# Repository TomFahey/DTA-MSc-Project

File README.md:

# DTA-MSc-Project

## Description

This repository contains the assorted code and schematics used in the design of a low-cost Differential Thermal Analysis device. This design utilises off-the-shelf parts, in
conjunction with open source software, to provide a kit-based setup allowing users to explore basic application of the DTA technique, in an intuitive and low-cost manner.

## Components

The parts used in this design include:

* Raspberry Pi 4 Model B, running RaspbianOS (buster)
* Raspberrry Pi Pico microcontroller
* Adafruit MAX31865 and MAX31856 temperature sensing breakout boards
* T-type thermocouple
* RTD sensors
* Cytron HAT-MDD10 motor controller board
* Adjustable DC Power Supply
* Custom PCB boards

## Structure

The repository consists of three main parts:

1) The webapp folder contains the python code and .ipynb notebooks which implement the widget-based user interface. This is intended to be run on a small board computer (SBC),
such as a Raspberry Pi Model B (preferably running Raspbian OS), using the JupyterLab web-based interactive development environment. voila-dashboard, is used as a server
extension within Jupyter, for deployment as a standalone web application.
2) The microcontroller folder contains the python code to be run on a CircuitPython compatible microcontroller (Raspberry Pi Pico), which interfaces with the SBC via USB.
3) The pcb folder contains the Autodesk Eagle files for the PCBs used by the system.

The systemd folder contains the configuration files used to automatically launch the service processes which setup the system. These should be placed in ``/etc/systemd/system/``.

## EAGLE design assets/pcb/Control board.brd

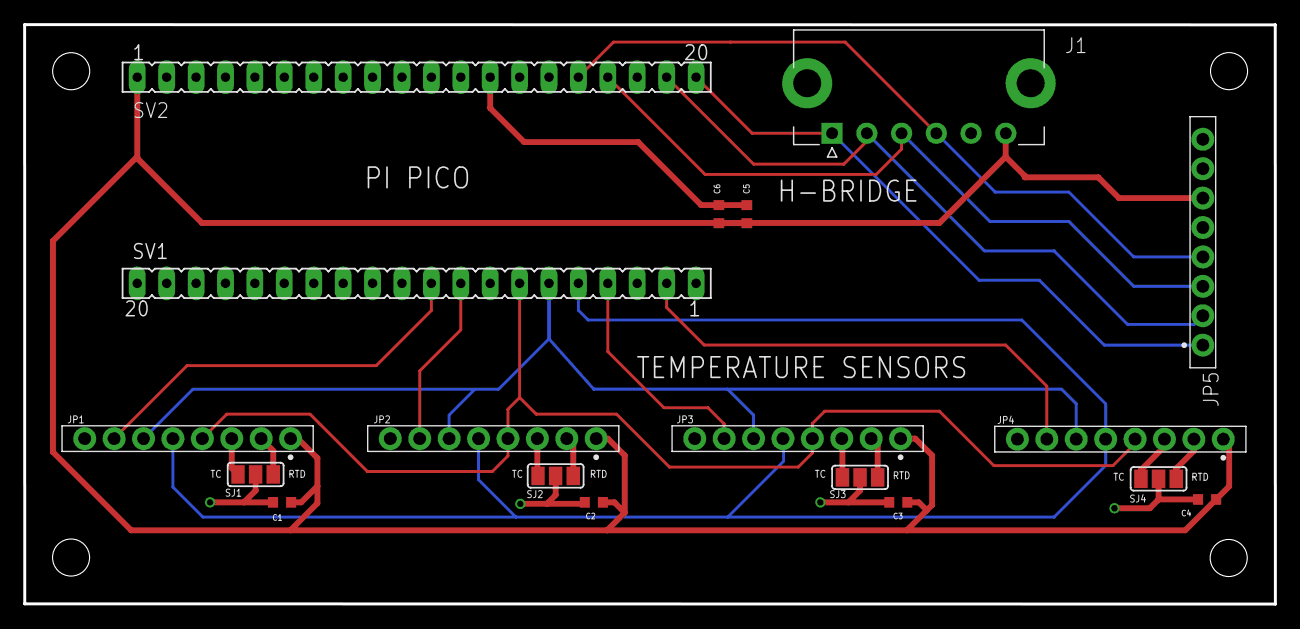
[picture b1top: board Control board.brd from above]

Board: 2 copper layers, 108.0 x 50.0 mm, 18 parts (0 on the bottom side), 21 nets.

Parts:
C1, C2, C3, C4, C5, C6: CL10A105KO8NNNC; CAPC1608X90N
J1: 436500603; MOLEX_436500603
JP1, JP2, JP3, JP4, JP5: HDRVR8W64P254_1X8_2159X200X810B
SJ1, SJ2, SJ3, SJ4: SJ_2
SV1, SV2: FE20

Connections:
+5V: C1.1, C2.1, C3.1, C4.1, C5.1, C6.1, J1.6, JP1.1, JP2.1, JP3.1, JP4.1, JP5.6, SV2.1
CLK: JP1.4, JP2.4, JP3.4, JP4.4, SV1.7
CS0: JP3.7, SV1.4
CS1: JP2.7, SV1.9
CS2: JP1.7, SV1.10
CS3: JP4.7, SV1.2
GND: C1.2, C2.2, C3.2, C4.2, C5.2, C6.2, J1.5, JP5.5, SJ1.2, SJ2.2, SJ3.2, SJ4.2, SV1.3, SV1.8, SV1.13, SV1.18, SV2.3, SV2.8, SV2.13, SV2.18
MISO: JP1.5, JP2.5, JP3.5, JP4.5, SV1.5
MOSI: JP1.6, JP2.6, JP3.6, JP4.6, SV1.6
unnamed: JP4.2, SJ4.1
unnamed: JP1.3, SJ1.3
unnamed: JP1.2, SJ1.1
unnamed: JP2.3, SJ2.3
unnamed: JP2.2, SJ2.1
unnamed: JP3.3, SJ3.3
unnamed: JP3.2, SJ3.1
unnamed: JP4.3, SJ4.3
PWM1: J1.1, JP5.1, SV2.20
PWM2: J1.2, JP5.2, SV2.19
PWM3: J1.3, JP5.3, SV2.17
PWM4: J1.4, JP5.4, SV2.16

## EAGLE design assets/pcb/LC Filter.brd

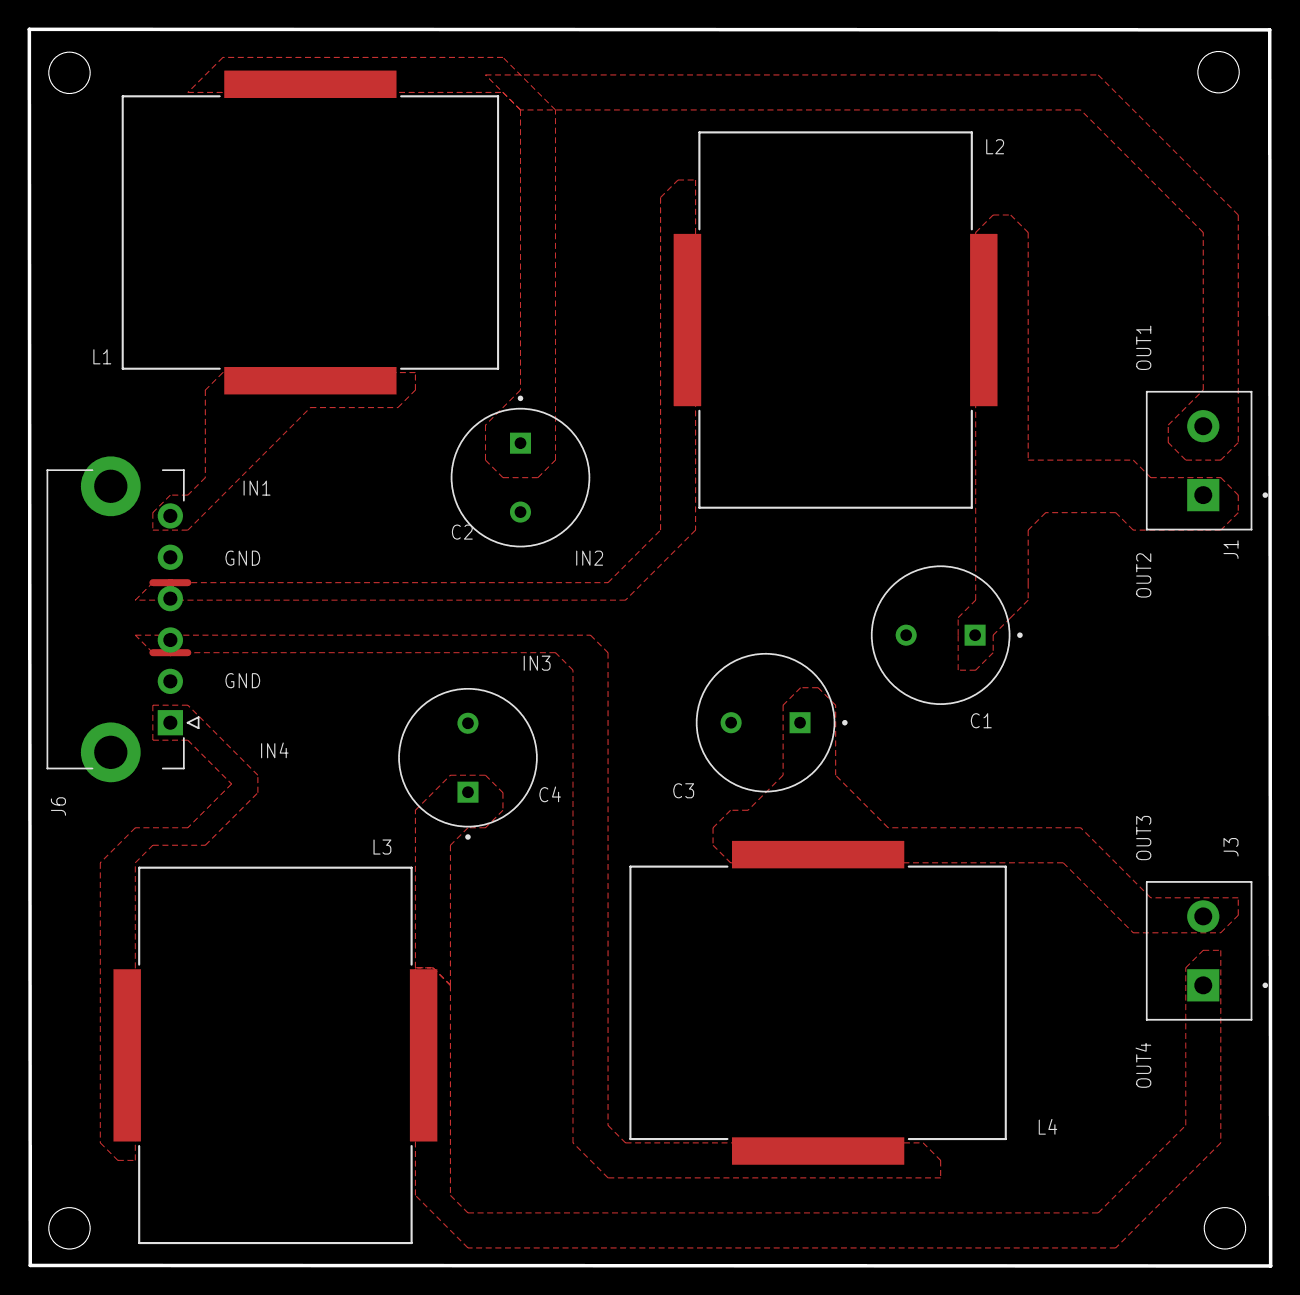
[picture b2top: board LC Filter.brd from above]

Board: 2 copper layers, 90.0 x 89.7 mm, 11 parts (0 on the bottom side), 9 nets.

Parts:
C1, C2, C3, C4: ECA1EHG471E; CAPPRD500W60D1000H1250
J1, J3: TB002-500-02BE; CUI_TB002-500-02BE
J6: 436500603; MOLEX_436500603
L1, L2, L3, L4: 60B104C; 6000B_SERIES_MUR

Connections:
GND: C1.N, C2.N, C3.N, C4.N, J6.2, J6.5
IN1: J6.6, L1.1
IN2: J6.4, L2.1
IN3: J6.3, L4.1
IN4: J6.1, L3.1
OUT1: C2.P, J1.2, L1.2
OUT2: C1.P, J1.1, L2.2
OUT3: C3.P, J3.2, L4.2
OUT4: C4.P, J3.1, L3.2

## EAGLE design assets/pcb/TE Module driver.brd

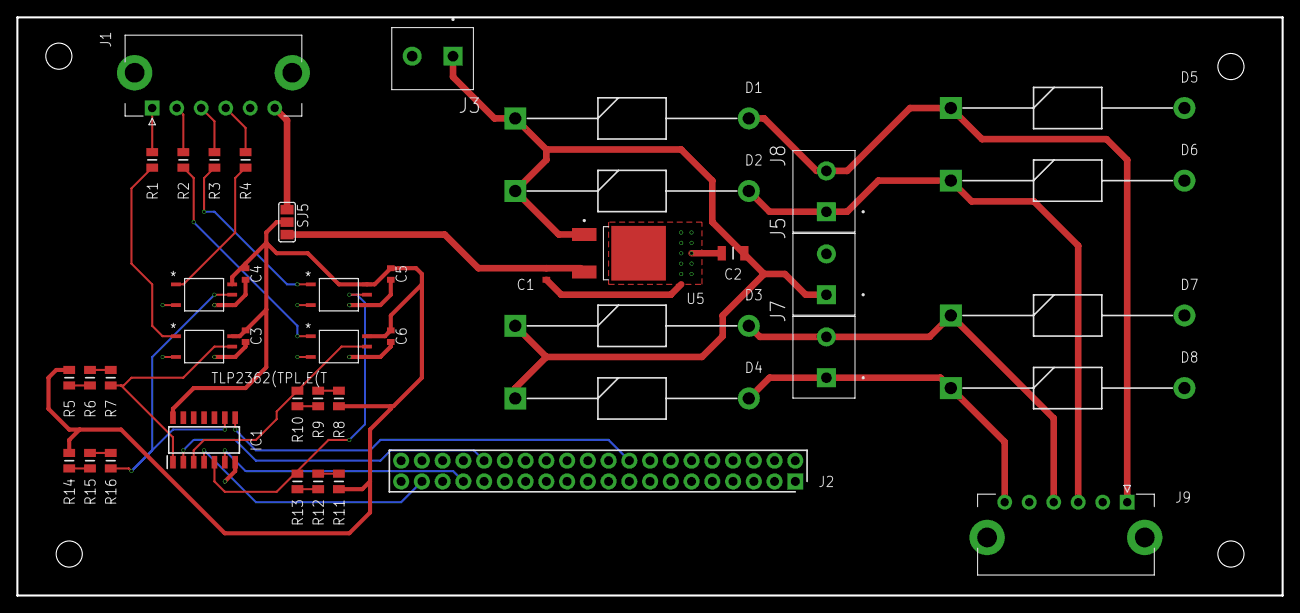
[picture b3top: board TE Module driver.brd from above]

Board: 2 copper layers, 154.9 x 70.8 mm, 44 parts (0 on the bottom side), 33 nets.

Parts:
C1, C3, C4, C5, C6: CL10B104KA8NNNC; CAPC1608X90N
C2: CL31B334KACNNNC; CAPC3216X140N
D1, D2, D3, D4, D5, D6, D7, D8: UF5408-E3_54; DIOAD2855W132L835D505
IC1: 74HCT14D,653; SOIC127P600X175-14N
J1, J9: 436500603; MOLEX_436500603
J2: M20-9762042; HDRV40W64P254_2X20_5080X508X83
J3, J5, J7, J8: TB002-500-02BE; CUI_TB002-500-02BE
R1, R2, R3, R4, R5, R6, R7, R8, R9, R10, R11, R12, R13, R14, R15, R16: 0805W8F1500T5E; RESC2013X65N
SJ5: SJ_2
U1, U2, U3, U4: TLP2362(TPL,E(T; 5PIN_SO6_TOS
U5: L78M05ABDT-TR; VREG_L78M05ABDT-TR

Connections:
+5V: C3.1, C4.1, C5.1, C6.1, IC1.14, R5.1, R8.1, R11.1, R14.1, SJ5.2, U1.6, U2.6, U3.6, U4.6
GND: C1.2, C2.2, C3.2, C4.2, C5.2, C6.2, D5.2, D6.2, D7.2, D8.2, IC1.7, J1.5, J2.6, J3.2, J5.2, J9.2, J9.5, U1.3, U1.4, U2.3, U2.4, U3.3, U3.4, U4.3, U4.4, U5.2
unnamed: J1.2, R2.1
unnamed: D4.2, D8.1, J7.1, J9.6
unnamed: D3.2, D7.1, J7.2, J9.4
unnamed: D2.2, D6.1, J8.1, J9.3
unnamed: D1.2, D5.1, J8.2, J9.1
unnamed: R2.2, U2.1
unnamed: R1.2, U1.1
unnamed: IC1.3, R10.2, U2.5
unnamed: IC1.5, R13.2, U3.5
unnamed: R3.2, U3.1
unnamed: R4.2, U4.1
unnamed: C1.1, SJ5.3, U5.3
unnamed: IC1.1, R7.2, U1.5
unnamed: R5.2, R6.2
unnamed: R6.1, R7.1
unnamed: J1.6, SJ5.1
unnamed: J1.1, R1.1
unnamed: J1.3, R3.1
unnamed: J1.4, R4.1
unnamed: R8.2, R9.2
unnamed: R9.1, R10.1
unnamed: R11.2, R12.2
unnamed: R12.1, R13.1
unnamed: IC1.9, R16.2, U4.5
unnamed: R14.2, R15.2
unnamed: R15.1, R16.1
PWM1: IC1.2, J2.32
PWM2: IC1.4, J2.37
PWM3: IC1.6, J2.33
PWM4: IC1.8, J2.18
VCC: C2.1, D1.1, D2.1, D3.1, D4.1, J3.1, J5.1, U5.1

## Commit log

2022-07-23 Refactored UI app, integrated asyncio streams
2022-07-28 Refactored microcontroller main program
2022-07-28 Added .gitignore
2022-07-28 Fixed .gitignore
2022-07-28 More fix .gitignore
2022-07-28 Tidy up project file structure
2022-07-28 Refactor receive.py, reversed server/client roles
2022-08-07 Updated receive.py to implement proper client/server communication model with webapp
2022-08-10 Rewrite of main webapp module, adopting client role instead of server, in conjunction with microcontroller interface program receive.py
2022-08-10 Implementation of basic helper classes ResponsiveDict and ResponsiveList, as well as prototype implementation of class capturing behaviour/characteristics of a DTA run
2022-08-10 Implementation of GUI "page", for adjusting parameters of DTA programme, through IPython widgets.
    Is imported by app.py, as a page or "tab" in webapp
2022-08-10 Setup script defining pin definitions and instantiation of library interface objects (such as Adafruit MAX31865 library).
2022-08-10 Removed reset functionality from PIDSensor class.
2022-08-10 Simple utility script to assist with debugging/development
2022-08-10 Modified Log class, changed function names for better comprehensibility, added start() function for interfacing with timeSensor class
2022-08-10 Modified function names and added self.config, for better cohesion with other modules
2022-08-10 Moved basic setup definitions/initialisations to setup.py script.
    Moved resposibility for controllinng runtime program flow inside Supervisor class.
2022-08-10 Added graphics displaying profile of configured DTA programme, as well as change in temperature
2022-08-10 Modified update() function of PIDState to allow for PID control of heating rate, as well as temperature, depending on mode.
2022-08-10 ResponsiveDict and ResponsiveList class, Programme class
2022-08-10 Changed details of connection teardown/start. Fixed bug with data_received function; added pickle serialisation of data objects, for transport over socket
2022-08-10 Module holding and maintaining global variables/configuration for webapp.py
    Also modifies configuration based on DTA programme and current readings.
2022-08-10 Added button control for up/down key presses, useful for setting programme configuration on touchscreen
2022-08-10 Updated doc string for ResponsiveDict()
2022-08-10 Added requirements.txt for webapp
2022-08-10 Moved requirements.txt up a directory to work with Binder
2022-08-10 Removed unnecessary dependency
2022-08-10 Unncessary dependency
2022-08-10 Fixed dependency issue
2022-08-10 Validation test data for temperature/heat PID control (in pickled binary form)
2022-08-10 More validation data
2022-08-11 Added jupyter notebook for interactive viewing of validation data
2022-08-11 Put jupyter lab code into convenience script
2022-08-11 Updated requirements.txt
2022-08-11 Missing dependency for bqplot
2022-08-19 Updated to allow cooling runs
2022-08-19 Updated to include deltaT readings
2022-08-19 Added reset button and functionality, as well as programme heating rate profile
2022-08-19 Added logging, connection reset and selective update
2022-08-19 Added support for thermocouple measurements, modified PID error calculation for heating mode, enabled PID configuration from webapp
2022-08-24 Added support for user definable time interval, as well as tracking of readings pushed to client, so only new readings are sent each update
2022-08-24 Minor refactoring of how PID values are handled
2022-08-24 Added page for saving recorded data.
    Updated requests so that new readings are appended to current series, rather than downloading entire series each request.
    Moved statements associated with reset button in UI to main() function (lines 120-130) of this module.
2022-08-24 Added configuration page for adjusting DTA system parameters such as PID parameters, as well as time interval between subsequent recordings
2022-08-24 Updated config attribute for Supervisor class, in line with changes in other modules
2022-08-24 Minor update to config attribute, in line with changes in other modules
2022-08-24 Added page view for selecting mountable drives under /media/pi/ (i.e usb disk drives) and filenames, for exporting saved data
2022-08-24 Moved statements associated with "reset" function to app.py module
2022-08-24 Renamed 'config.py' to 'programme.py', so that 'config.py' can be used for third page (adjusting PID params + interval)
2022-08-24 Small updates to allow compabatibility with newer datasets, whilst retaining compatability of older ones.
2022-08-24 IPython notebook for exploring timing of subroutines on Pico
2022-08-25 Changed serial update period to be half the defined interval time
2022-08-25 Better use of import statemenet for asyncio (less problems with using reload)
    Refactoring global variables from settings module
2022-08-25 Tidied up work function
    Removed uneccesary 'reading' variable
    Removed unecessary sleep at end of main() function
2022-08-25 Improved import statement for asyncio
    Refactoring of attributes belonging to settings module
    Bugfix for reset() function, due to index error
    Removed use of importlib's reload (unecessary)
2022-08-25 Refactoring for attributes belonging to settings module
    Removed use of unecessary reload() from importlib in reset() function
2022-08-25 Refactored global attributes to prevent confusion in different namespaces
2022-09-13 Adjust UI dimensions
2022-09-13 Separate working file from production
2022-09-13 Change default file loaded
2022-09-17 Added EAGLE PCB files
2022-12-09 Ignore unnecessary browser generated files
2022-12-09 Typo
2022-12-09 Get rid of cache files
2023-01-11 Fixed bug of delta T readout not updating
2023-01-11 Typo on array index
2023-01-16 Ignore draft rewrite of receive.py - server.py
2023-01-16 Changed so time stamps start when main() runs
2023-01-16 Ignore unused libs (pyRTOS) and testing files
2023-01-16 Ignore .mpy
2023-01-16 Tidy up boot file, enable usb_cdc
2023-01-16 Added precision attribute to TempSensor class
2023-01-16 Replaced global variables with class attributes in other modules, added additional sensors
2023-01-16 Missed pyRTOS file in .gitignore
2023-01-16 Big refactor, implementing better naming. settings.py -> shared.py, configure.py -> programme.py, config.py -> settings.py, file.py -> export.py
2023-01-16 Included refactor changes relating to previous commit, added unicode symbols for better text labelling, added legend to graph, made line colors more visually distinct, changed limits for right axis t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
2023-01-16 Included changes relating to refactor
2023-01-16 Added configuration options for filter frequency, cold junction disable, baudrate and auto-conversion to class constructor
2023-01-16 Added systemd unit files for automatic startup
2023-01-16 ipywidgets requirement 7.7 -> 8.0.4. Adds multi-touch drag for slider widgets.
2023-01-16 Ignore unused file
2023-02-10 Updated values plotted on graph to show received data
2023-02-10 Updated appState to include new data values
2023-02-10 Updated AppState class to include new data values
2023-02-10 Updated for new data values (TEMPA, TEMPB etc.)
2023-02-16 Create initial README.md
    Initial README explaining motivation of project, components required and general structure of repository.
2023-02-22 Updated readme for introduction of Sphinx docs
    Modified readme from Markdown format to reStructuredText, in accordance with introduction of Sphinx documentation.
2023-02-22 Fix formatting typo
2023-02-22 Ignore Sphinx build directory, virtualenv, .vscode
2023-02-22 Added pyserial-asyncio to requirements
2023-02-22 Ignore data/debugging jupyter files
2023-02-22 Replaced Mardown README file for ReStructuredText
2023-02-22 Initial start on Sphinx docs
2023-02-22 Ignore data folder in webapp folder
2023-02-22 Rewrite of docstring for ResponsiveDict class
2023-02-23 Initial start on Sphinx documentation for project
2023-02-24 Added Getting Started content
2023-02-25 Rework project tree structure
2023-02-25 Tidy up restructure
2023-02-25 Remove untracked files
2023-02-25 Additional to last commit
2023-02-25 Additional to previous commit
2023-02-26 Worked on Sphinx docs for webapp modules
2023-02-26 Added Sphinx docs for export.py, utils.py, settings.py
2023-02-26 Update Sphinx docs conf.py for publishing to Github pages
2023-02-27 Add Sphinx build files for Github Pages
2023-02-27 Move html build files to docs folder
2023-02-27 More documentation for dashboard application
2023-02-27 Move sphinx docs source files to docsrc directory
2023-02-27 Add dotfiles to /docs build folder
2023-02-27 Update sphinx docs to latest build
2023-02-27 Finished sphinx docs for webapp modules, updated basic usage section
2023-02-28 Worked on basic and advanced usage pages
2023-03-01 Added docs for log.py, client.py for microcontroller code
2023-03-01 Added docs for utils.py, setup.py and PID.py in microcontroller code
2023-03-02 Updated installation instructions
2023-03-02 Updated README with link to docs
2023-03-02 Update docs build
2023-03-02 Correct typo in installation instructions
2023-03-02 Ignore unused files in microcontroller code
2023-03-02 Updated seutp instructions and systemd service files
2023-03-02 Updated doc build
2023-03-02 Updated debugging documentation
2023-03-04 Tweaked UI docs for better clarity on module layout
2023-03-06 Added docs for webapp app.py
2023-03-11 Fixed incorrect filepath in systemd service files
2023-03-11 Corrected filepath typo on setup page
2023-03-21 Updated Hardware, Advanced Usage and Debugging sections
2023-05-02 Updated documentation for MCU software reference
2023-05-03 Updated micro-example
2023-05-04 Finished microcontroller software example docs.
2023-05-04 Added some hyperlinks in example docs

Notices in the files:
parts and their libraries:
COPYRIGHT: Copyright (C) 2022 Ultra Librarian. All rights reserved.
